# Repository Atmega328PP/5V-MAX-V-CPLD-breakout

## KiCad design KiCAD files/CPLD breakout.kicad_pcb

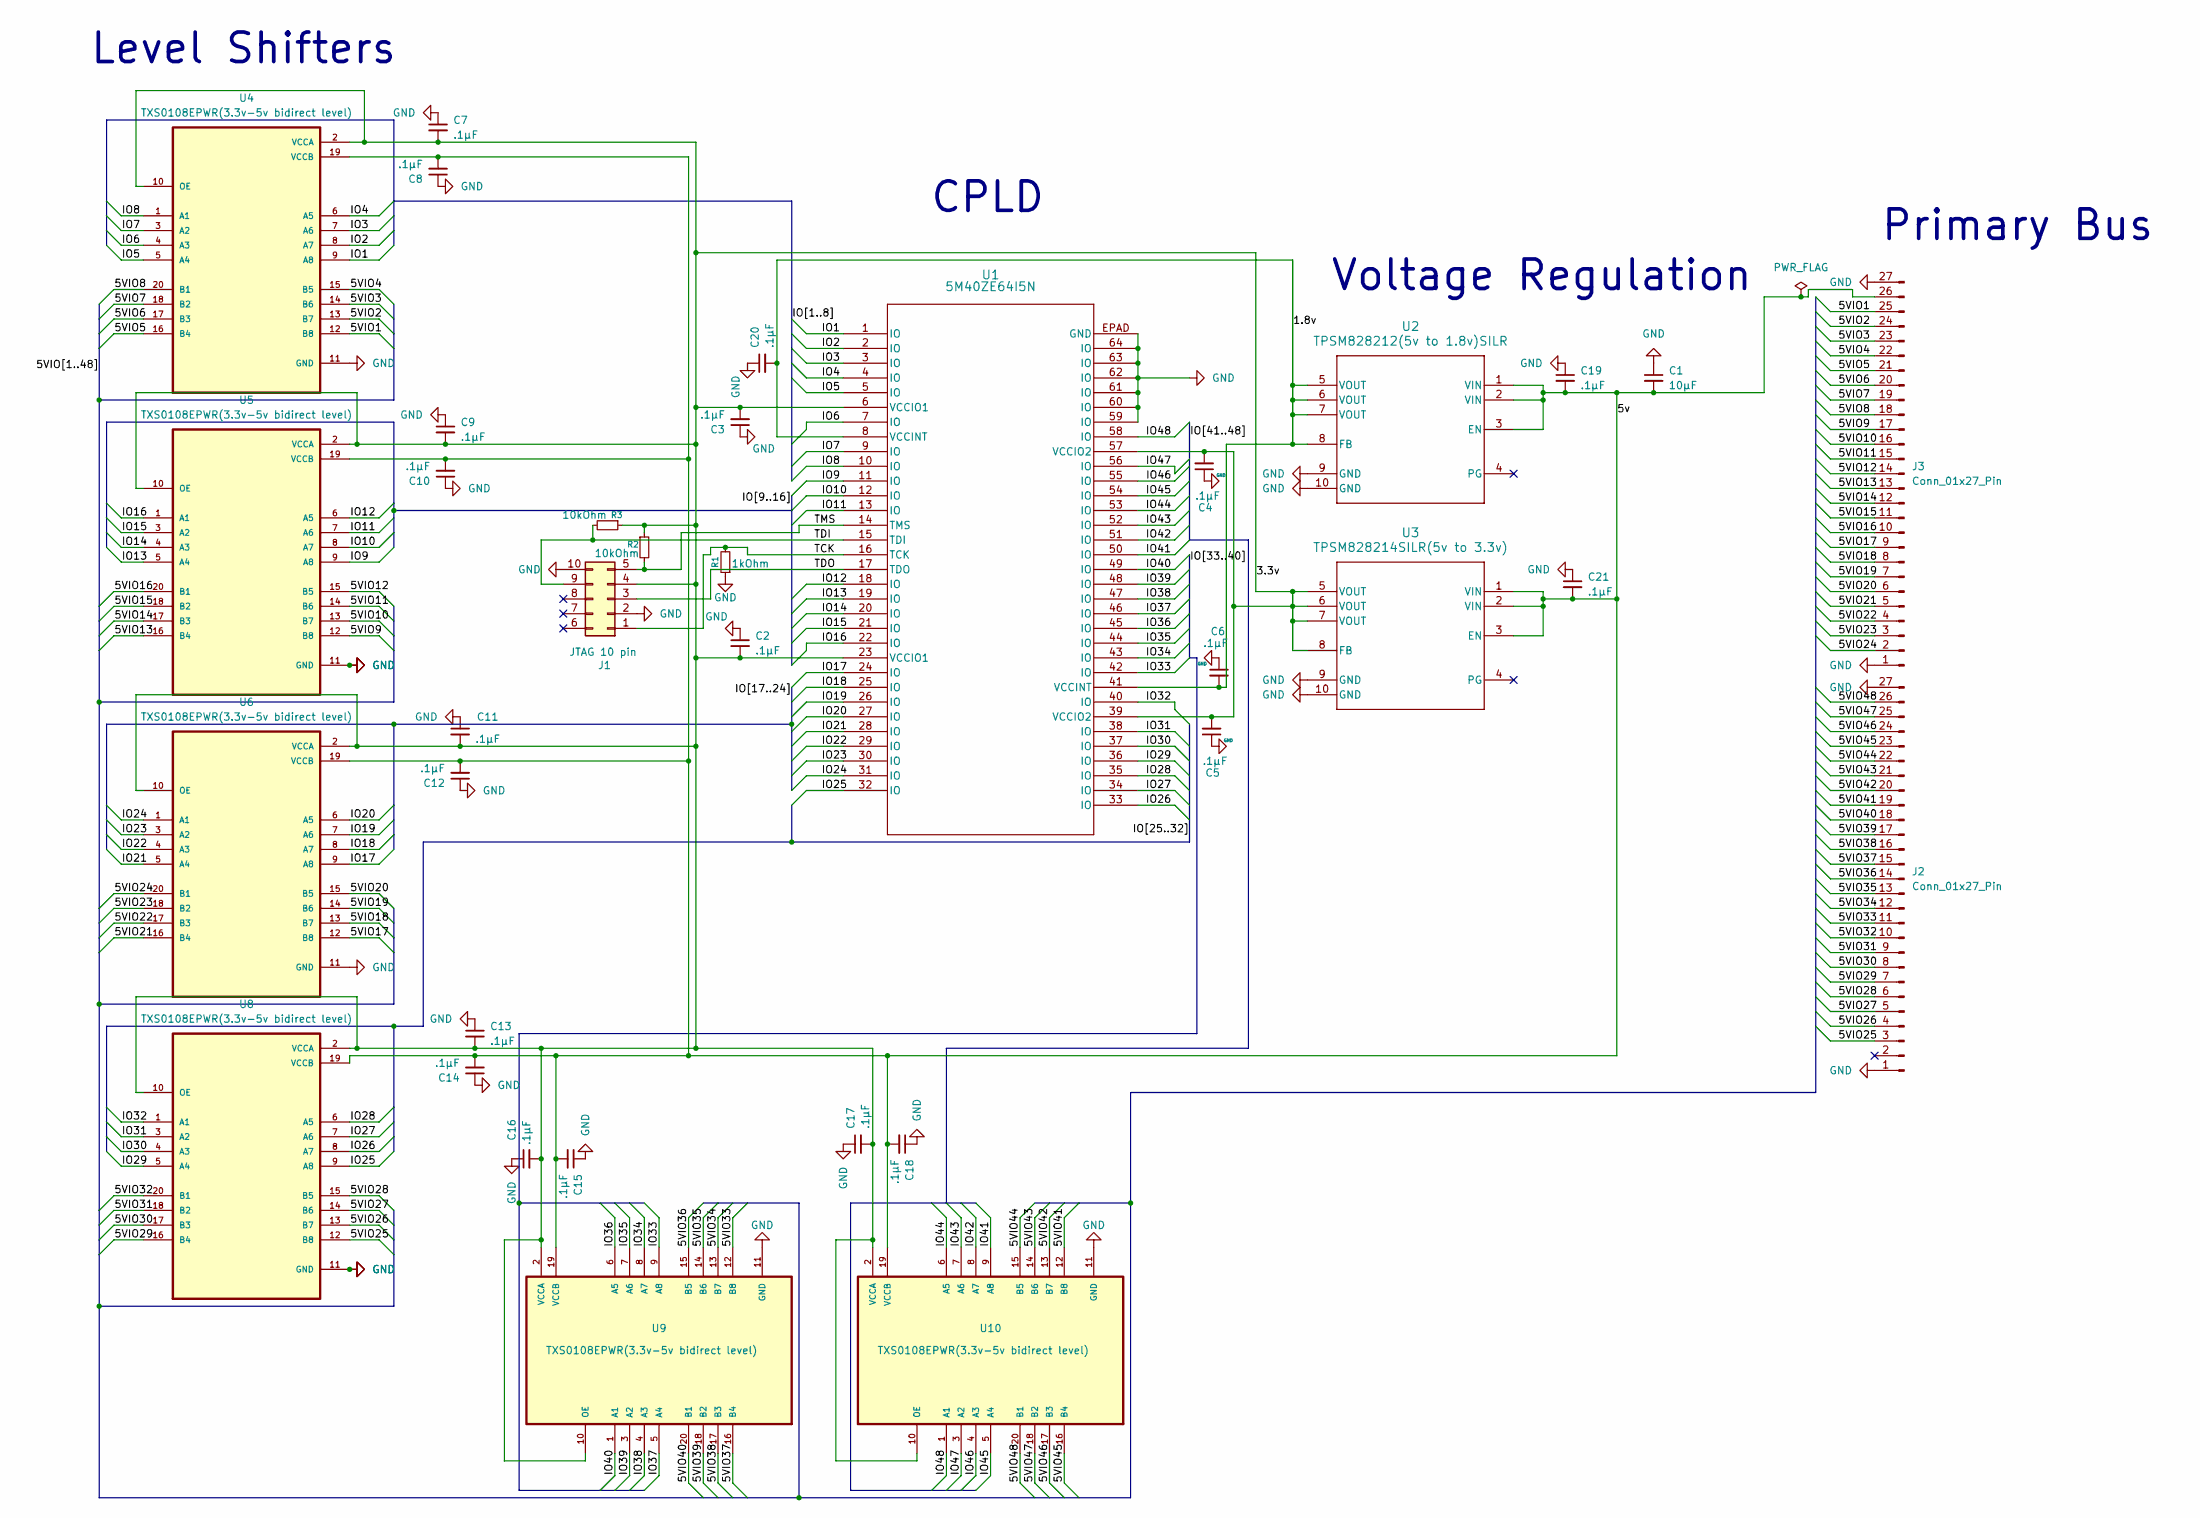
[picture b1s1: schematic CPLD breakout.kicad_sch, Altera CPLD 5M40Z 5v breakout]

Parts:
C1: 10μF; C_0805_2012Metric
C2, C3, C4, C5, C6, C7, C8, C9, C10, C11, C12, C13, C14, C15, C16, C17, C18, C19, C20, C21: .1μF; C_0805_2012Metric
J1: JTAG 10 pin; IDC-Header_2x05_P2.54mm_Vertical
J2, J3: Conn_01x27_Pin; PinHeader_1x27_P2.54mm_Vertical
R1: 1kOhm; R_0805_2012Metric
R2, R3: 10kOhm; R_0805_2012Metric
U1: 5M40ZE64I5N; EQFP64_A_1P2-D2_4P5_INT
U2: TPSM828212(5v to 1.8v)SILR; TPSM828212SILR(5v to 1.8v)
U3: TPSM828214SILR(5v to 3.3v)
U4, U5, U6, U8, U9, U10: TXS0108EPWR(3.3v-5v bidirect level); SOP65P640X120-20N(3.3v-5v bidirect shift)

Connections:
/1.8v: C6.2, C20.2, U1.8 (VCCINT), U1.41 (VCCINT), U2.5 (VOUT), U2.6 (VOUT), U2.7 (VOUT), U2.8 (FB)
/3.3v: C2.2, C3.2, C4.2, C5.2, C7.2, C9.2, C11.2, C13.2, C16.2, C17.2, J1.4, R2.1, R3.1, U1.6 (VCCIO1), U1.23 (VCCIO1), U1.39 (VCCIO2), U1.57 (VCCIO2), U3.5 (VOUT), U3.6 (VOUT), U3.7 (VOUT), U3.8 (FB), U4.2 (VCCA), U4.10 (OE), U5.2 (VCCA), U5.10 (OE), U6.2 (VCCA), U6.10 (OE), U8.2 (VCCA), U8.10 (OE), U9.2 (VCCA), U9.10 (OE), U10.2 (VCCA), U10.10 (OE)
/5VIO1: J3.25, U4.12 (B8)
/5VIO2: J3.24, U4.13 (B7)
/5VIO3: J3.23, U4.14 (B6)
/5VIO4: J3.22, U4.15 (B5)
/5VIO5: J3.21, U4.16 (B4)
/5VIO6: J3.20, U4.17 (B3)
/5VIO7: J3.19, U4.18 (B2)
/5VIO8: J3.18, U4.20 (B1)
/5VIO9: J3.17, U5.12 (B8)
/5VIO10: J3.16, U5.13 (B7)
/5VIO11: J3.15, U5.14 (B6)
/5VIO12: J3.14, U5.15 (B5)
/5VIO13: J3.13, U5.16 (B4)
/5VIO14: J3.12, U5.17 (B3)
/5VIO15: J3.11, U5.18 (B2)
/5VIO16: J3.10, U5.20 (B1)
/5VIO17: J3.9, U6.12 (B8)
/5VIO18: J3.8, U6.13 (B7)
/5VIO19: J3.7, U6.14 (B6)
/5VIO20: J3.6, U6.15 (B5)
/5VIO21: J3.5, U6.16 (B4)
/5VIO22: J3.4, U6.17 (B3)
/5VIO23: J3.3, U6.18 (B2)
/5VIO24: J3.2, U6.20 (B1)
/5VIO25: J2.3, U8.12 (B8)
/5VIO26: J2.4, U8.13 (B7)
/5VIO27: J2.5, U8.14 (B6)
/5VIO28: J2.6, U8.15 (B5)
/5VIO29: J2.7, U8.16 (B4)
/5VIO30: J2.8, U8.17 (B3)
/5VIO31: J2.9, U8.18 (B2)
/5VIO32: J2.10, U8.20 (B1)
/5VIO33: J2.11, U9.12 (B8)
/5VIO34: J2.12, U9.13 (B7)
/5VIO35: J2.13, U9.14 (B6)
/5VIO36: J2.14, U9.15 (B5)
/5VIO37: J2.15, U9.16 (B4)
/5VIO38: J2.16, U9.17 (B3)
/5VIO39: J2.17, U9.18 (B2)
/5VIO40: J2.18, U9.20 (B1)
/5VIO41: J2.19, U10.12 (B8)
/5VIO42: J2.20, U10.13 (B7)
/5VIO43: J2.21, U10.14 (B6)
/5VIO44: J2.22, U10.15 (B5)
/5VIO45: J2.23, U10.16 (B4)
/5VIO46: J2.24, U10.17 (B3)
/5VIO47: J2.25, U10.18 (B2)
/5VIO48: J2.26, U10.20 (B1)
/5v: C1.2, C8.2, C10.2, C12.2, C14.2, C15.2, C18.2, C19.2, C21.2, J3.26, U2.1 (VIN), U2.2 (VIN), U2.3 (EN), U3.1 (VIN), U3.2 (VIN), U3.3 (EN), U4.19 (VCCB), U5.19 (VCCB), U6.19 (VCCB), U8.19 (VCCB), U9.19 (VCCB), U10.19 (VCCB)
/IO1: U1.1 (IO), U4.9 (A8)
/IO2: U1.2 (IO), U4.8 (A7)
/IO3: U1.3 (IO), U4.7 (A6)
/IO4: U1.4 (IO), U4.6 (A5)
/IO5: U1.5 (IO), U4.5 (A4)
/IO6: U1.7 (IO), U4.4 (A3)
/IO7: U1.9 (IO), U4.3 (A2)
/IO8: U1.10 (IO), U4.1 (A1)
/IO9: U1.11 (IO), U5.9 (A8)
/IO10: U1.12 (IO), U5.8 (A7)
/IO11: U1.13 (IO), U5.7 (A6)
/IO12: U1.18 (IO), U5.6 (A5)
/IO13: U1.19 (IO), U5.5 (A4)
/IO14: U1.20 (IO), U5.4 (A3)
/IO15: U1.21 (IO), U5.3 (A2)
/IO16: U1.22 (IO), U5.1 (A1)
/IO17: U1.24 (IO), U6.9 (A8)
/IO18: U1.25 (IO), U6.8 (A7)
/IO19: U1.26 (IO), U6.7 (A6)
/IO20: U1.27 (IO), U6.6 (A5)
/IO21: U1.28 (IO), U6.5 (A4)
/IO22: U1.29 (IO), U6.4 (A3)
/IO23: U1.30 (IO), U6.3 (A2)
/IO24: U1.31 (IO), U6.1 (A1)
/IO25: U1.32 (IO), U8.9 (A8)
/IO26: U1.33 (IO), U8.8 (A7)
/IO27: U1.34 (IO), U8.7 (A6)
/IO28: U1.35 (IO), U8.6 (A5)
/IO29: U1.36 (IO), U8.5 (A4)
/IO30: U1.37 (IO), U8.4 (A3)
/IO31: U1.38 (IO), U8.3 (A2)
/IO32: U1.40 (IO), U8.1 (A1)
/IO33: U1.42 (IO), U9.9 (A8)
/IO34: U1.43 (IO), U9.8 (A7)
/IO35: U1.44 (IO), U9.7 (A6)
/IO36: U1.45 (IO), U9.6 (A5)
/IO37: U1.46 (IO), U9.5 (A4)
/IO38: U1.47 (IO), U9.4 (A3)
/IO39: U1.48 (IO), U9.3 (A2)
/IO40: U1.49 (IO), U9.1 (A1)
/IO41: U1.50 (IO), U10.9 (A8)
/IO42: U1.51 (IO), U10.8 (A7)
/IO43: U1.52 (IO), U10.7 (A6)
/IO44: U1.53 (IO), U10.6 (A5)
/IO45: U1.54 (IO), U10.5 (A4)
/IO46: U1.55 (IO), U10.4 (A3)
/IO47: U1.56 (IO), U10.3 (A2)
/IO48: U1.58 (IO), U10.1 (A1)
/TCK: J1.1, R1.2, U1.16 (TCK)
/TDI: J1.9, R3.2, U1.15 (TDI)
/TDO: J1.3, U1.17 (TDO)
/TMS: J1.5, R2.2, U1.14 (TMS)
GND: C1.1, C2.1, C3.1, C4.1, C5.1, C6.1, C7.1, C8.1, C9.1, C10.1, C11.1, C12.1, C13.1, C14.1, C15.1, C16.1, C17.1, C18.1, C19.1, C20.1, C21.1, J1.2, J1.10, J2.1, J2.27, J3.1, J3.27, R1.1, U1.59 (IO), U1.60 (IO), U1.61 (IO), U1.62 (IO), U1.63 (IO), U1.64 (IO), U1.EPAD (GND), U2.9 (GND), U2.10 (GND), U3.9 (GND), U3.10 (GND), U4.11 (GND), U5.11 (GND), U6.11 (GND), U8.11 (GND), U9.11 (GND), U10.11 (GND)

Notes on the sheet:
CPLD
Level Shifters
Voltage Regulation
Primary Bus

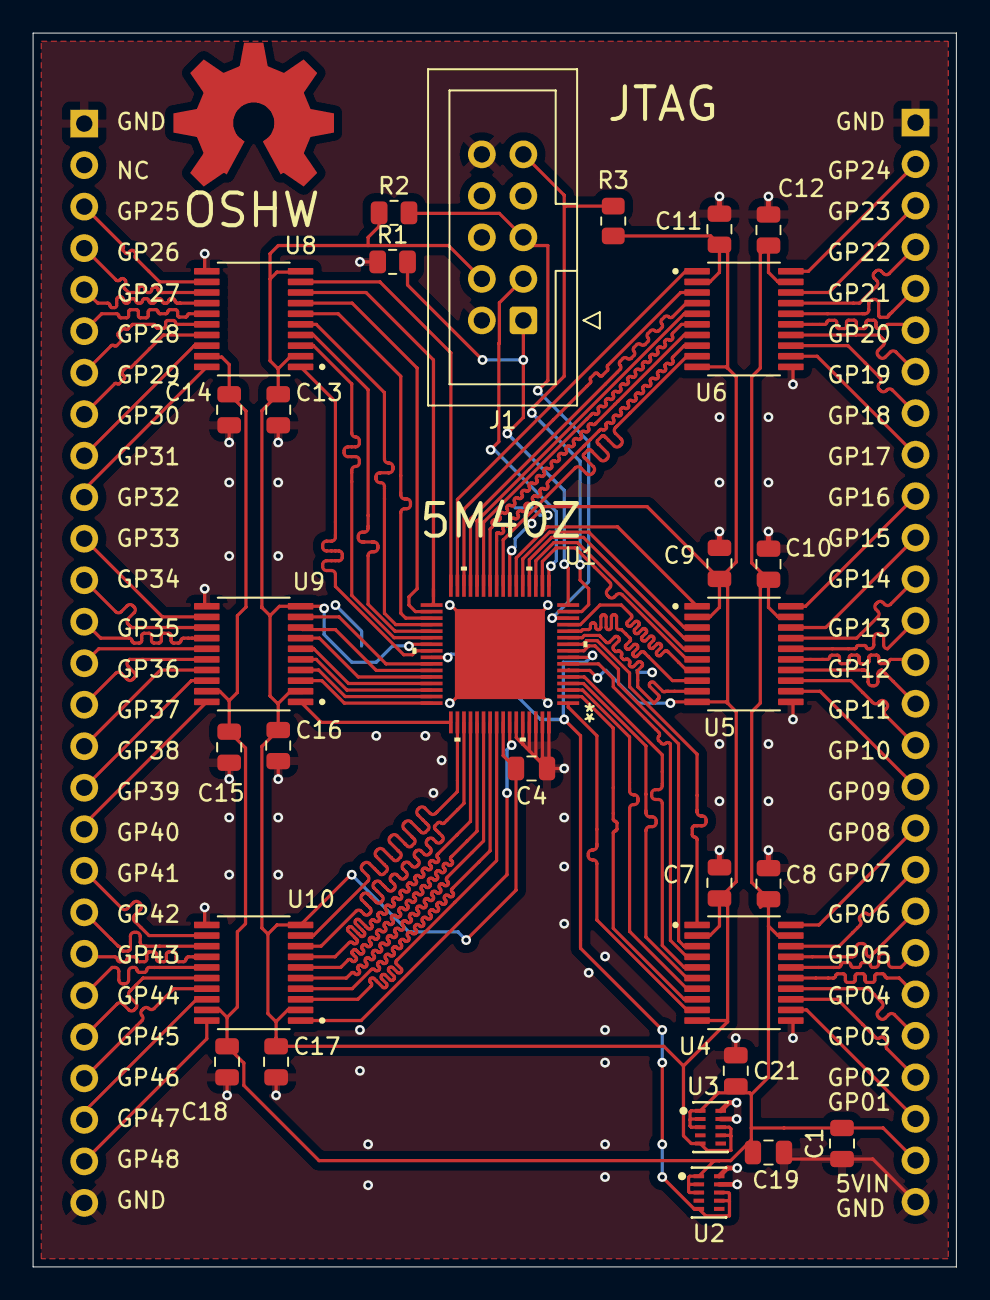
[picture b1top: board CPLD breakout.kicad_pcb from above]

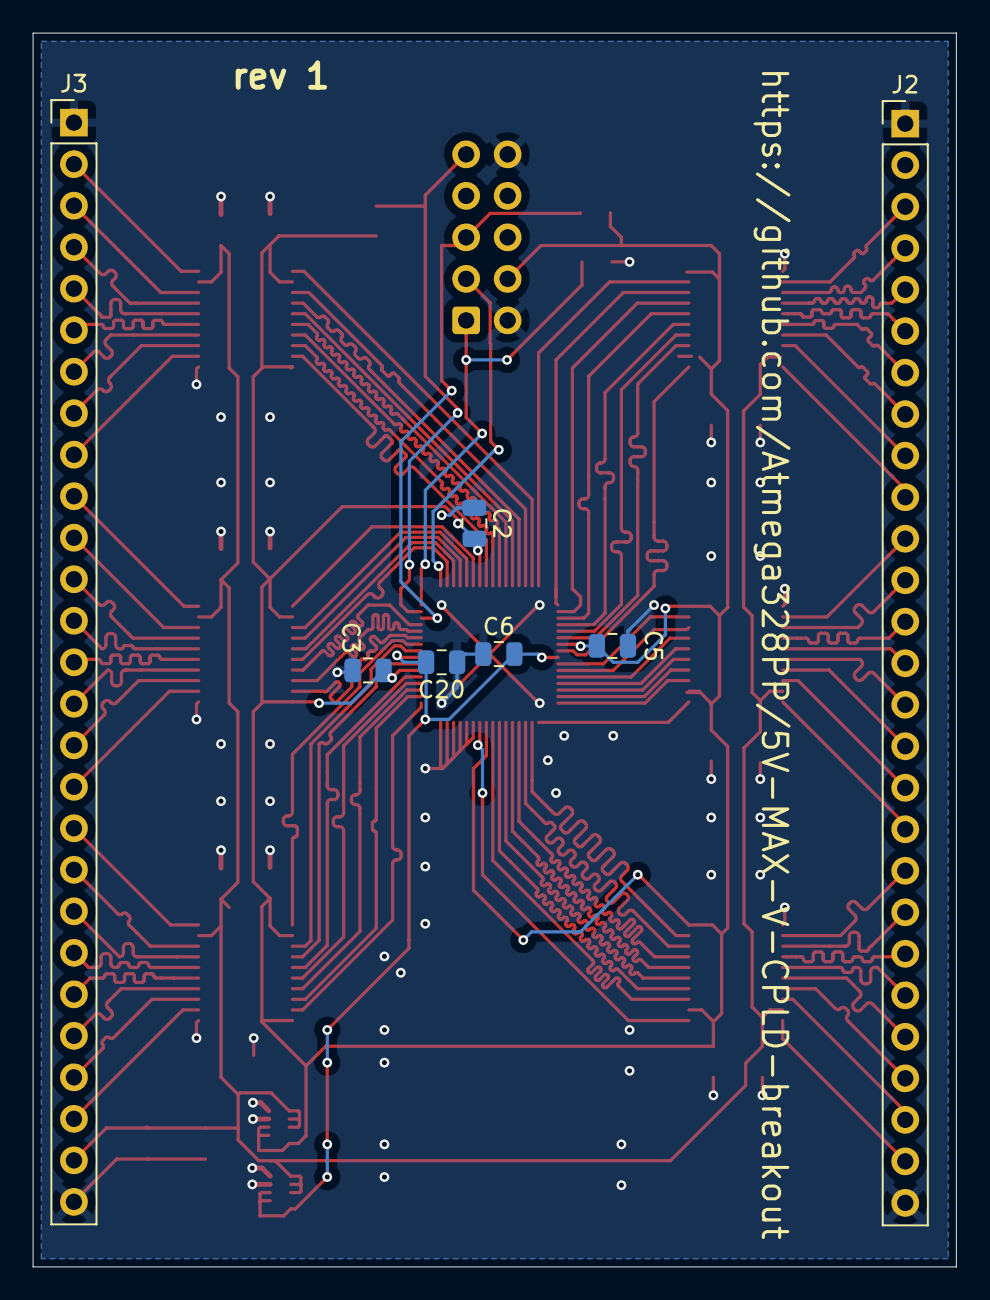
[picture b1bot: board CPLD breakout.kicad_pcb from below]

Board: 2 copper layers, 56.5 x 75.5 mm, 37 parts (7 on the bottom side), 104 nets.

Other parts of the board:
OSHW_COPPER_10MM: VAL**; OSHW_COPPER_10MM

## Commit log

2025-11-28 Create licence
2025-12-01 Uploading new board and drill files
    Added "rev 1" to the bottom silkscreen and generated the new corresponding gerber drill files in a .zip
2025-12-01 Update README.md to include the JTAG header
2025-12-01 Added Bill of Materials
2025-12-01 Rename Bill of Materials.md to Bill of Materials.txt
